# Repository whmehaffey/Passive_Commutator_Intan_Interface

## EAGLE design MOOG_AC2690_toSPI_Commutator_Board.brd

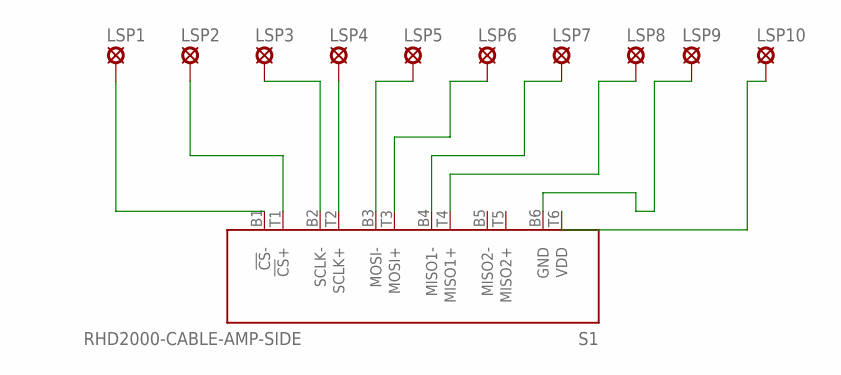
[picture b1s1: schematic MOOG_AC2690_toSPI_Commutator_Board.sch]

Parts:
LSP1, LSP2, LSP3, LSP4, LSP5, LSP6, LSP7, LSP8, LSP9, LSP10: LSP11
S1: RHD2000-CABLE-AMP-SIDE; OMNETICS_PZN-12-AA

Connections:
unnamed: LSP1.MP, S1.B1 (!CS!-)
unnamed: LSP2.MP, S1.T1 (!CS!+)
unnamed: LSP3.MP, S1.B2 (SCLK-)
unnamed: LSP4.MP, S1.T2 (SCLK+)
unnamed: LSP5.MP, S1.B3 (MOSI-)
unnamed: LSP6.MP, S1.T3 (MOSI+)
unnamed: LSP7.MP, S1.B4 (MISO1-)
unnamed: LSP8.MP, S1.T4 (MISO1+)
unnamed: LSP9.MP, S1.B6 (GND)
unnamed: LSP10.MP, S1.T6 (VDD)

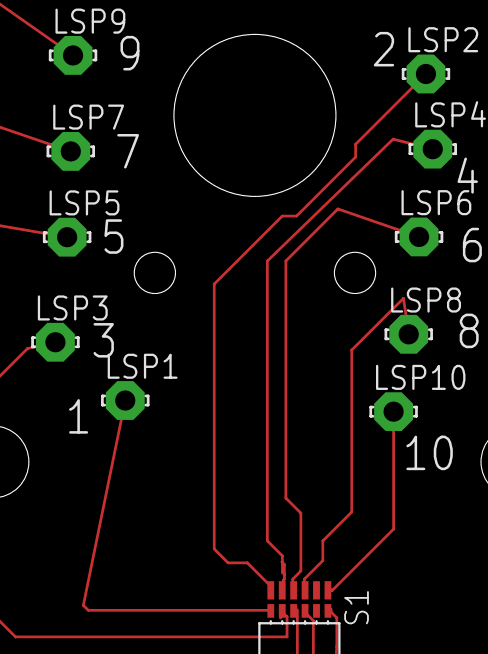
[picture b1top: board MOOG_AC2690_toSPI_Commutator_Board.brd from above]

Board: 2 copper layers, 11 parts (0 on the bottom side), 10 nets.

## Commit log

2018-09-08 First Upload
    First Version, only tested once.
2018-09-08 CleanUp
    Removed extra file (copy of .BRD file)
